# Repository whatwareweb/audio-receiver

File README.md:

# audio-receiver
OSHW audio reciever and amplifier

### What is it
This is an audio receiver and amplifier with a classic design. I built it because I wanted to learn more about Class AB amplifier design and analog circuitry in general.

### Why use it
Class-D amplifiers, as used in receivers these days, offer lots of power, but the sound quality can be lacking.

Class-AB amplifiers, while less efficient and therefore harder to get high power output, have overall less distortion and can offer a better signal-to-noise ratio if designed properly.

The design of the amplifier portion is similar to amplifiers built in the so-called "Golden age" of Hi-fi audio, in the 70s and 80s. I wanted a Class-AB amplifier that had the great sound quality of products from times gone by, but with modern features such as digital screens, and without the clunky mechanical interfaces of older receivers.

### Goals
My goals for this project were to have good sound quality with modern features, and also to use industry standard practices for receiver assembly to make it easy to assemble.

### Features
 - Stereo audio amplifier
 - 4 input channels
 - Volume control
 - Digitally selectable inputs
 - OLED display with renamable inputs
 - 15w per channel output
 - All-analog signal path
 - 3 separate PCBs for low noise

### Usage
It is super simple, just hook up a line level signal to the RCA jacks on the back, and select your input and you're good to go!

### Wiring
To wire up the internal parts, simply connect the +/-5v line from the first power supply to the input board, the +5v line to the control board, and the +36v line from the 2nd power supply to the amplifier board, as shown in the PCB silkscreen. Then, using the Phoenix cables in the BOM, connect the Phoenix connectors together. 

### PCB screenshots

## BOM
|Qty|Value                          |Mouser URL                                                                                                                             |Mouser PN            |price|lumped price|
|---|-------------------------------|---------------------------------------------------------------------------------------------------------------------------------------|---------------------|-----|------------|
|2  |10uF                           |https://www.mouser.com/ProductDetail/Wurth-Elektronik/860020672010?qs=sGAEpiMZZMsh%252B1woXyUXj4jKQI6sNRw6%252B%2FnWw7D23Ww%3D         |710-860020672010     |0.11 |0.22        |
|6  |100uF                          |https://www.mouser.com/ProductDetail/Nichicon/UVR1H101MPD1TD?qs=sGAEpiMZZMsh%252B1woXyUXj9Qfu%2FLgQWnHf9Zyy1TLY94%3D                   |647-UVR1H101MPD1TD   |0.25 |1.5         |
|2  |100pF                          |https://www.mouser.com/ProductDetail/Walsin/YP501101K040BAND5P?qs=sGAEpiMZZMsh%252B1woXyUXj9Vc%2FsqQGnyVc97Ek7nEcX0%3D                 |791-YP501101K40AND5  |0.11 |0.22        |
|2  |2200uF                         |https://www.mouser.com/ProductDetail/Rubycon/35YXJ2200M16X25?qs=sGAEpiMZZMsh%252B1woXyUXj57M5zdvZVAFuY6LrCottNI%3D                     |232-35YXJ2200M16X25  |1.15 |2.3         |
|2  |33uF                           |https://www.mouser.com/ProductDetail/Wurth-Elektronik/860010672011?qs=sGAEpiMZZMsh%252B1woXyUXj4jKQI6sNRw6%2FzsPRxKesag%3D             |710-860010672011     |0.12 |0.24        |
|2  |100nF                          |https://www.mouser.com/ProductDetail/Walsin/YV101103Z060HAND5P?qs=sGAEpiMZZMsh%252B1woXyUXj9Vc%2FsqQGnyVkbUw7FMjgKQ%3D                 |791-YV101103Z60HAND5 |0.1  |0.2         |
|8  |1N4148                         |https://www.mouser.com/ProductDetail/onsemi-Fairchild/1N4148-T50R?qs=sGAEpiMZZMtbRapU8LlZD%252B6h%2FWulpAkrNJDKqwRgmZcB5SlWjKcc2w%3D%3D|512-1N4148T50R       |0.1  |0.8         |
|8  |UF4004                         |https://www.mouser.com/ProductDetail/Diotec-Semiconductor/UF4004?qs=OlC7AqGiEDlRgKmeDlLF1Q%3D%3D                                       |637-UF4004           |0.12 |0.96        |
|1  |Fuse Holder                    |https://www.mouser.com/ProductDetail/Eaton-Electronics/BK-1A5601?qs=sfCJykTDjbAGESUvg%2FlMZw%3D%3D                                     |504-1A5601           |0.5  |0.5         |
|1  |Screw_Terminal_01x03           |https://www.mouser.com/ProductDetail/Phoenix-Contact/1757255?qs=uD%2FdkN7XIa0ez8xszzicKg%3D%3D                                         |651-1757255          |0.93 |0.93        |
|1  |Screw_Terminal_01x04           |https://www.mouser.com/ProductDetail/Same-Sky/TB007-508-04BE?qs=vLWxofP3U2wnrmN2C1kFLw%3D%3D                                           |490-TB007-508-04BE   |0.94 |0.94        |
|1  |Screw_Terminal_01x02           |https://www.mouser.com/ProductDetail/Same-Sky/TB007-508-02BE?qs=vLWxofP3U2y6PFKAfCqKUQ%3D%3D                                           |490-TB007-508-02BE   |0.49 |0.49        |
|2  |BC559                          |https://www.mouser.com/ProductDetail/Diotec-Semiconductor/BC559A?qs=OlC7AqGiEDlWVUSYP2ErFQ%3D%3D                                       |637-BC559A           |0.1  |0.2         |
|4  |BD139                          |https://www.mouser.com/ProductDetail/STMicroelectronics/BD139-16?qs=RfHREzyZwW%252BVwEMhVd3zpQ%3D%3D                                   |511-BD139-16         |0.62 |2.48        |
|2  |BD140                          |https://www.mouser.com/ProductDetail/STMicroelectronics/BD140-16?qs=RfHREzyZwW%252BkgnSLCtGbjg%3D%3D                                   |511-BD140-16         |0.45 |0.9         |
|2  |MJE3055                        |https://www.mouser.com/ProductDetail/onsemi/MJE3055TG?qs=HVbQlW5zcXUpZ6jjVRRo8A%3D%3D                                                  |863-MJE3055TG        |0.85 |1.7         |
|2  |MJE2955                        |https://www.mouser.com/ProductDetail/onsemi/MJE2955TG?qs=HVbQlW5zcXV0Q1cBURTsUg%3D%3D                                                  |863-MJE2955TG        |1.23 |2.46        |
|4  |33k                            |https://www.mouser.com/ProductDetail/YAGEO/MFR-25FTF52-33K?qs=gt1LBUVyoHmEHRwLqpWLLA%3D%3D                                             |603-MFR-25FTF52-33K  |0.1  |0.4         |
|8  |2k2                            |https://www.mouser.com/ProductDetail/YAGEO/MF0207FTE52-2K2?qs=KUIzHt%2Fe91lZCf2OHy2lbw%3D%3D                                           |603-MF0207FTE52-2K2  |0.1  |0.8         |
|2  |100R                           |https://www.mouser.com/ProductDetail/YAGEO/MFR-12FTF52-100R?qs=oAGoVhmvjhzHogggiomzAA%3D%3D                                            |603-MFR-12FTF52-100R |0.1  |0.2         |
|2  |1k                             |https://www.mouser.com/ProductDetail/YAGEO/MFR-25FTF52-1K?qs=Uzd%2Fwh%252BZzhBCS7HxlKfPkQ%3D%3D                                        |603-MFR-25FTF52-1K   |0.1  |0.2         |
|2  |560                            |https://www.mouser.com/ProductDetail/YAGEO/FMP200JR-52-560R?qs=wcZjbqjoJehIyDJh2zs3Bw%3D%3D                                            |603-FMP200JR-52-560R |0.15 |0.3         |
|4  |2R7                            |https://www.mouser.com/ProductDetail/YAGEO/SQP500JB-2R7?qs=sGAEpiMZZMsPqMdJzcrNwl88Wd0KdECunjP3GAgCqls%3D                              |603-SQP500JB-2R7     |0.54 |2.16        |
|2  |12k                            |https://www.mouser.com/ProductDetail/YAGEO/MFR25SFTF26-12K?qs=sGAEpiMZZMsPqMdJzcrNwqpmsrDQJrmxnqH2%2F1fJqXZRHayDc4k%252B4A%3D%3D       |603-MFR25SFTF26-12K  |0.1  |0.2         |
|2  |2R7                            |https://www.mouser.com/ProductDetail/YAGEO/CFR-25JR-52-2R7?qs=sGAEpiMZZMsPqMdJzcrNwiPCnpFTGbbhiVnCR3xqnQk%3D                           |603-CFR-25JR-52-2R7  |0.1  |0.2         |
|2  |100nF                          |https://www.mouser.com/ProductDetail/Walsin/RD21B104K500A5HAND?qs=ZrPdAQfJ6DNDZtFW9mG29g%3D%3D                                         |791-RD21B104K500A5HA |0.19 |0.38        |
|2  |10uF                           |https://www.mouser.com/ProductDetail/TDK/FG28X5R1E106MRT06?qs=LtAzLad%252BoeUoMYHhhxs3zA%3D%3D                                         |810-FG28X5R1E106MR06 |0.45 |0.9         |
|1  |PJRAS4X2U01AUX                 |https://www.mouser.com/ProductDetail/Switchcraft/PJRAS4X2U01X?qs=mcPJWgAPNreWN%252BuSt4UsAA%3D%3D                                      |502-PJRAS4X2U01X     |5.22 |5.22        |
|1  |Screw_Terminal_01x04           |https://www.mouser.com/ProductDetail/Phoenix-Contact/1757268?qs=uD%2FdkN7XIa2BicmSj3mD7g%3D%3D                                         |651-1757268          |1.26 |1.26        |
|1  |Screw_Terminal_01x03           |https://www.mouser.com/ProductDetail/Phoenix-Contact/1757255?qs=uD%2FdkN7XIa0ez8xszzicKg%3D%3D                                         |651-1757255          |0.93 |0.93        |
|1  |Screw_Terminal_01x03           |https://www.mouser.com/ProductDetail/Same-Sky/TB007-508-03BE?qs=vLWxofP3U2zHYiGqNs1vAA%3D%3D                                           |490-TB007-508-03BE   |0.72 |0.72        |
|1  |CD4052B                        |https://www.mouser.com/c/?q=595-CD4052BE                                                                                               |595-CD4052BE         |0.6  |0.6         |
|1  |100nF                          |https://www.mouser.com/ProductDetail/Walsin/RD21B104K500A5HAND?qs=ZrPdAQfJ6DNDZtFW9mG29g%3D%3D                                         |791-RD21B104K500A5HA |0.19 |0.19        |
|1  |Screw_Terminal_01x04           |https://www.mouser.com/ProductDetail/Phoenix-Contact/1757268?qs=uD%2FdkN7XIa2BicmSj3mD7g%3D%3D                                         |651-1757268          |1.26 |1.26        |
|1  |Screw_Terminal_01x02           |https://www.mouser.com/ProductDetail/Same-Sky/TB007-508-02BE?qs=vLWxofP3U2y6PFKAfCqKUQ%3D%3D                                           |490-TB007-508-02BE   |0.49 |0.49        |
|5  |SW_Push                        |https://www.mouser.com/ProductDetail/Same-Sky/TS02-66-55-BK-260-LCR-D?qs=A6eO%252BMLsxmT6x4NEvNu8bQ%3D%3D                              |179-TS026655BK260LCR |0.1  |0.5         |
|1  |ATtiny84A-SS                   |https://www.mouser.com/ProductDetail/Microchip-Technology/ATTINY84A-SSFR?qs=TI%2F9gtmDCEEVjKMalwq6aQ%3D%3D                             |556-ATTINY84A-SSFR   |1.08 |1.08        |
|4  |heatsinks                      |https://www.mouser.com/ProductDetail/Same-Sky/HSS-B20-NP-12?qs=u4fy%2FsgLU9Mva%2Fp9%252ByZBdw%3D%3D                                    |n/a                  |0.59 |2.36        |
|1  |m3 bolts                       |https://www.homedepot.com/p/Hillman-M3-0-5-x-10-mm-Internal-Hex-Button-Head-Cap-Screws-20-Pack-44456/204801187                         |n/a                  |5.74 |5.74        |
|1  |m3 nuts                        |https://www.homedepot.com/p/Hillman-Metric-Hex-Nuts-M3-x-0-50-Coarse-Thread-4053/204801247                                             |n/a                  |6.62 |6.62        |
|1  |fuse holder                    |https://www.mouser.com/ProductDetail/Eaton-Electronics/BK-1A5601?qs=sfCJykTDjbAGESUvg%2FlMZw%3D%3D                                     |n/a                  |0.5  |0.5         |
|2  |fuses                          |https://www.mouser.com/ProductDetail/Schurter/0034.1519?qs=ar9f0rk5DXBZIZv2oGoEHA%3D%3D                                                |n/a                  |0.47 |0.94        |
|2  |red terminal post              |https://www.mouser.com/ProductDetail/SparkFun/PRT-09739?qs=WyAARYrbSnb2d3ZiFmZgWQ%3D%3D                                                |n/a                  |0.75 |1.5         |
|2  |black terminal post            |https://www.mouser.com/ProductDetail/SparkFun/PRT-09740?qs=WyAARYrbSnbVb9GdE8xnVA%3D%3D                                                |n/a                  |0.75 |1.5         |
|2  |internal phoenix connector 3pin|https://www.mouser.com/ProductDetail/Phoenix-Contact/1757022?qs=sGAEpiMZZMvlX3nhDDO4ANTLkcKs1Zj3jcphtS8o9Tk%3D                         |n/a                  |2.89 |5.78        |
|2  |internal phoenix connector 4pin|https://www.mouser.com/ProductDetail/Phoenix-Contact/1757035?qs=sGAEpiMZZMvlX3nhDDO4AH7PhxHWF%252BlKb5jy%252B%2F%252BeCXE%3D           |n/a                  |3.85 |7.7         |
|1  |fan                            |https://a.co/d/h5aS2CF                                                                                                                 |n/a                  |15.95|15.95       |
|1  |dip16 socket                   |https://www.mouser.com/ProductDetail/TE-Connectivity/1-2199298-4?qs=fK8dlpkaUMvpL10rY9Abiw%3D%3D                                       |n/a                  |0.25 |0.25        |
|1  |36v psu                        |https://www.mouser.com/ProductDetail/MEAN-WELL/LRS-150-36?qs=vDxCgdWo2h82V5jS5IXvUQ%3D%3D                                              |n/a                  |19.8 |19.8        |
|1  |+ / - 5v psu                   |https://www.mouser.com/ProductDetail/MEAN-WELL/PD-2505?qs=V9a8iPeg90ze2O5SXmOiQQ%3D%3D                                                 |n/a                  |16   |16          |
|1  |oled display                   |https://a.co/d/fhCKttE                                                                                                                 |n/a                  |6.29 |6.29        |
|1  |Input switcher PCB             |n/a – pcbway                                                                                                                           |n/a                  |5    |5           |
|1  |control board pcb              |n/a – pcbway                                                                                                                           |n/a                  |5    |5           |
|1  |amp board pcb                  |n/a – pcbway                                                                                                                           |n/a                  |27.78|27.78       |
|   |                               |                                                                                                                                       |                     |     |            |
|   |                               |                                                                                                                                       |                     |     |            |
|   |                               |                                                                                                                                       |                     |     |            |
|   |                               |                                                                                                                                       |                     |     |            |
|   |                               |                                                                                                                                       |                     |     |            |
|   |                               |                                                                                                                                       |                     |     |            |
|   |                               |                                                                                                                                       |                     |     |            |
|   |Total                          |                                                                                                                                       |                     |     |            |
|   |163.74                         |                                                                                                                                       |                     |     |            |

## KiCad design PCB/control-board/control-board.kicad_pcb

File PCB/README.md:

# audio-receiver
OSHW audio reciever and amplifier

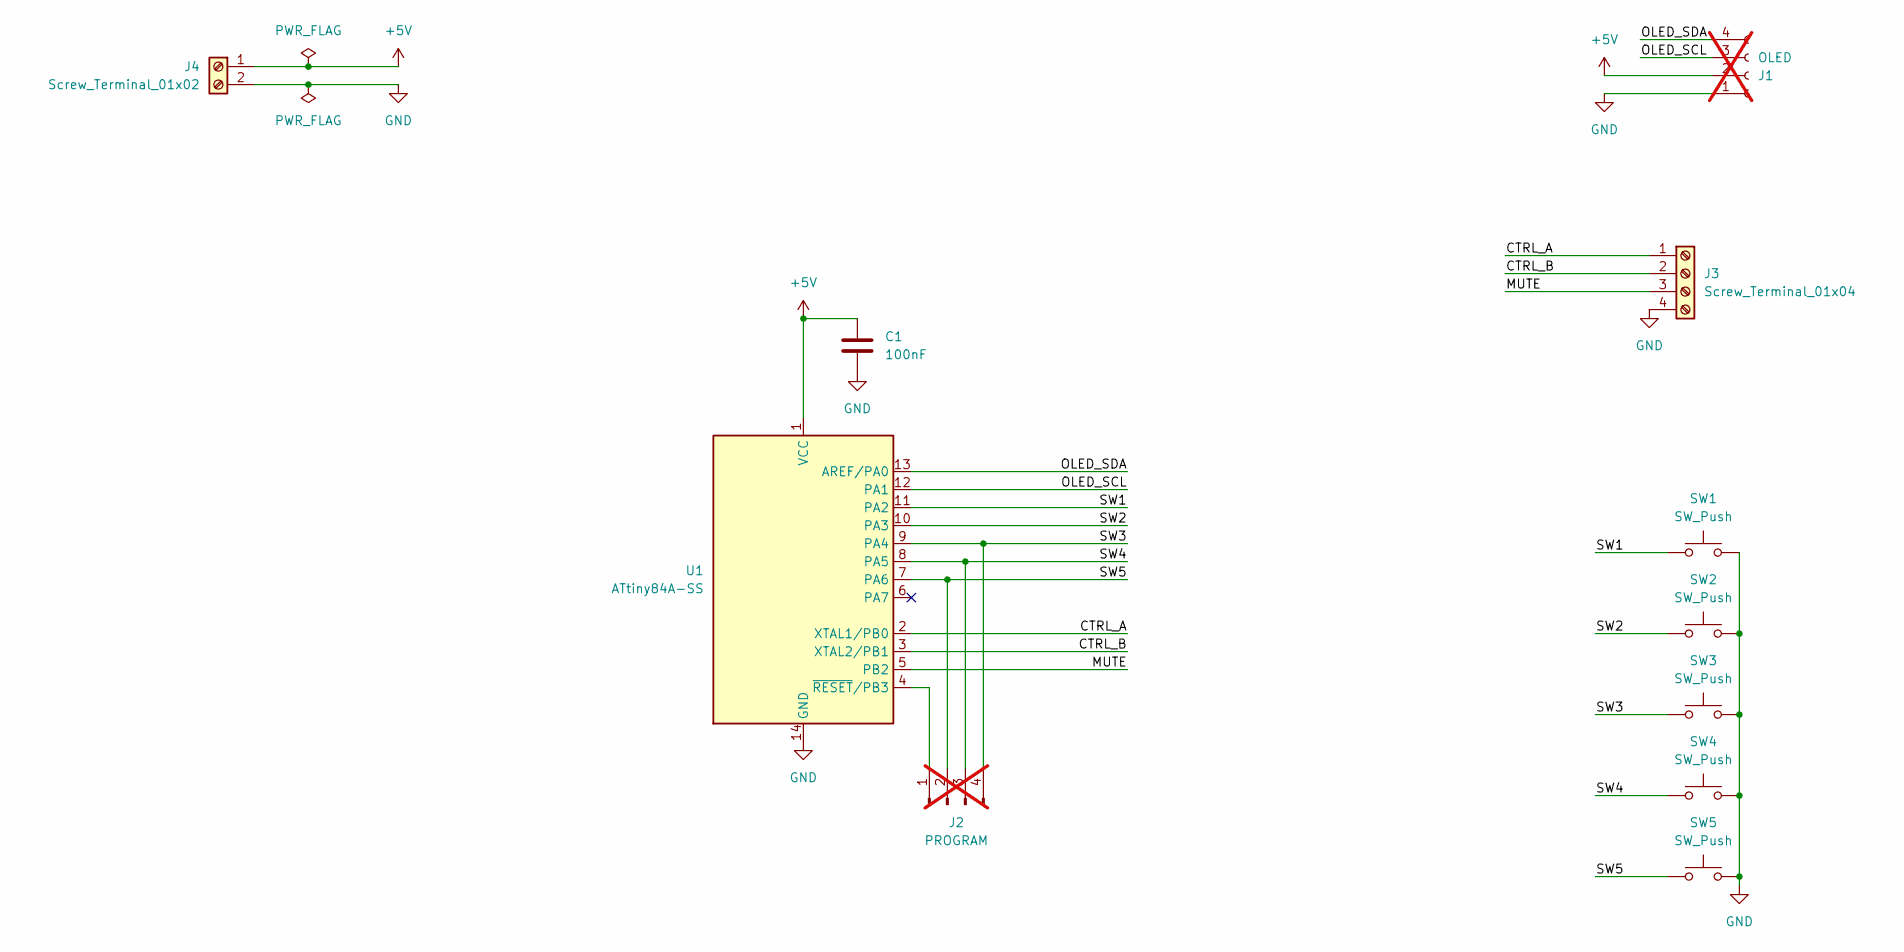
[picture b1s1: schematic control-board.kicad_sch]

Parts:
C1: 100nF; C_Disc_D6.0mm_W2.5mm_P5.00mm; Mouser PN 791-RD21B104K500A5HA
J1: OLED; SSD1306-0.91-OLED-4pin-128x32; not fitted
J2: PROGRAM; PinHeader_1x04_P2.54mm_Vertical; not fitted
J3: Screw_Terminal_01x04; PhoenixContact_MSTBA_2,5_4-G-5,08_1x04_P5.08mm_Horizontal; Mouser PN 651-1757268
J4: Screw_Terminal_01x02; TerminalBlock_CUI_TB007-508-02_1x02_P5.08mm_Horizontal; Mouser PN 490-TB007-508-02BE
SW1, SW2, SW3, SW4, SW5: SW_Push; SW_PUSH_6mm; Mouser PN 179-TS026655BK260LCR
U1: ATtiny84A-SS; SOIC-14_3.9x8.7mm_P1.27mm; Mouser PN 556-ATTINY84A-SSFR

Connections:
+5V: C1.1, J1.2, J4.1, U1.1 (VCC)
/CTRL_A: J3.1, U1.2 (XTAL1/PB0)
/CTRL_B: J3.2, U1.3 (XTAL2/PB1)
/MUTE: J3.3, U1.5 (PB2)
/OLED_SCL: J1.3, U1.12 (PA1)
/OLED_SDA: J1.4, U1.13 (AREF/PA0)
/SW1: SW1.1, U1.11 (PA2)
/SW2: SW2.1, U1.10 (PA3)
/SW3: J2.4, SW3.1, U1.9 (PA4)
/SW4: J2.3, SW4.1, U1.8 (PA5)
/SW5: J2.2, SW5.1, U1.7 (PA6)
GND: C1.2, J1.1, J3.4, J4.2, SW1.2, SW2.2, SW3.2, SW4.2, SW5.2, U1.14 (GND)
unnamed: J2.1, U1.4 (~RESET/PB3)

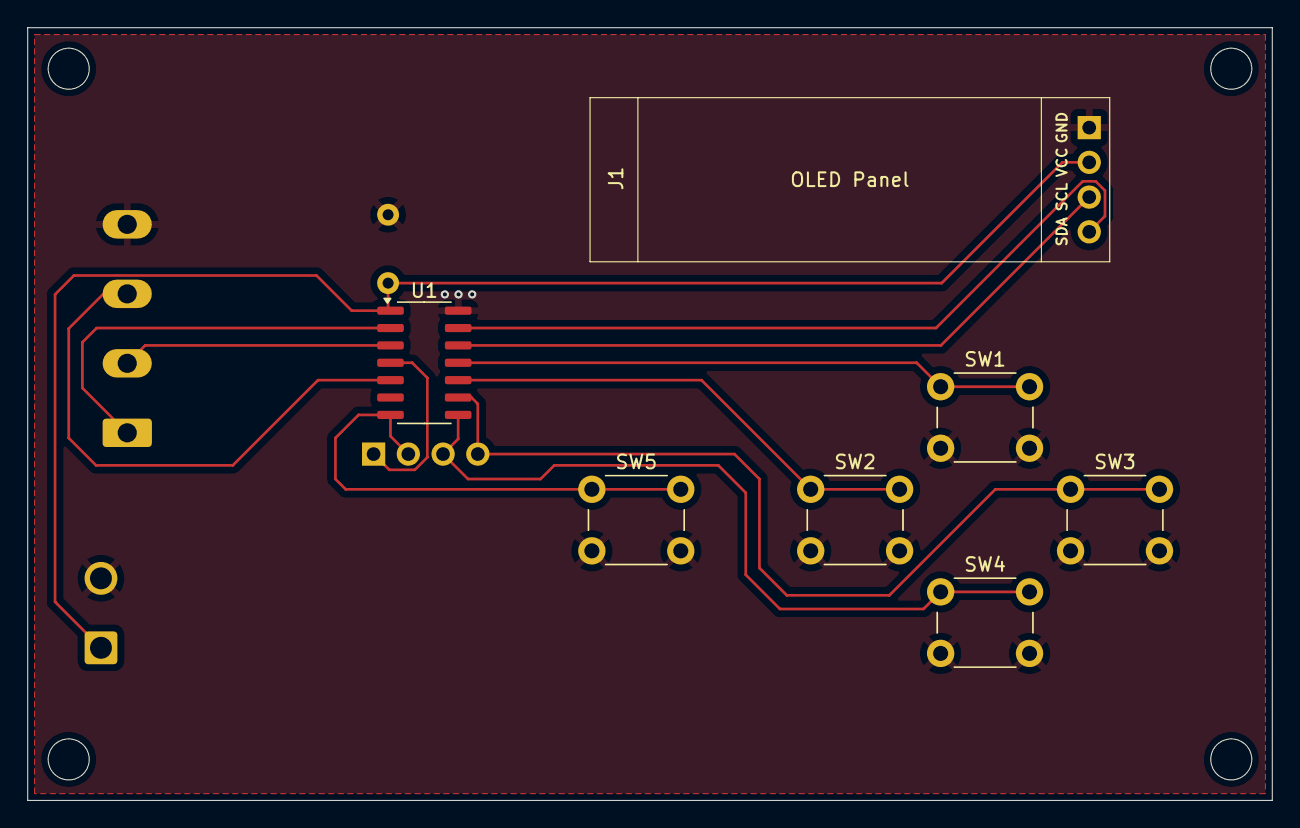
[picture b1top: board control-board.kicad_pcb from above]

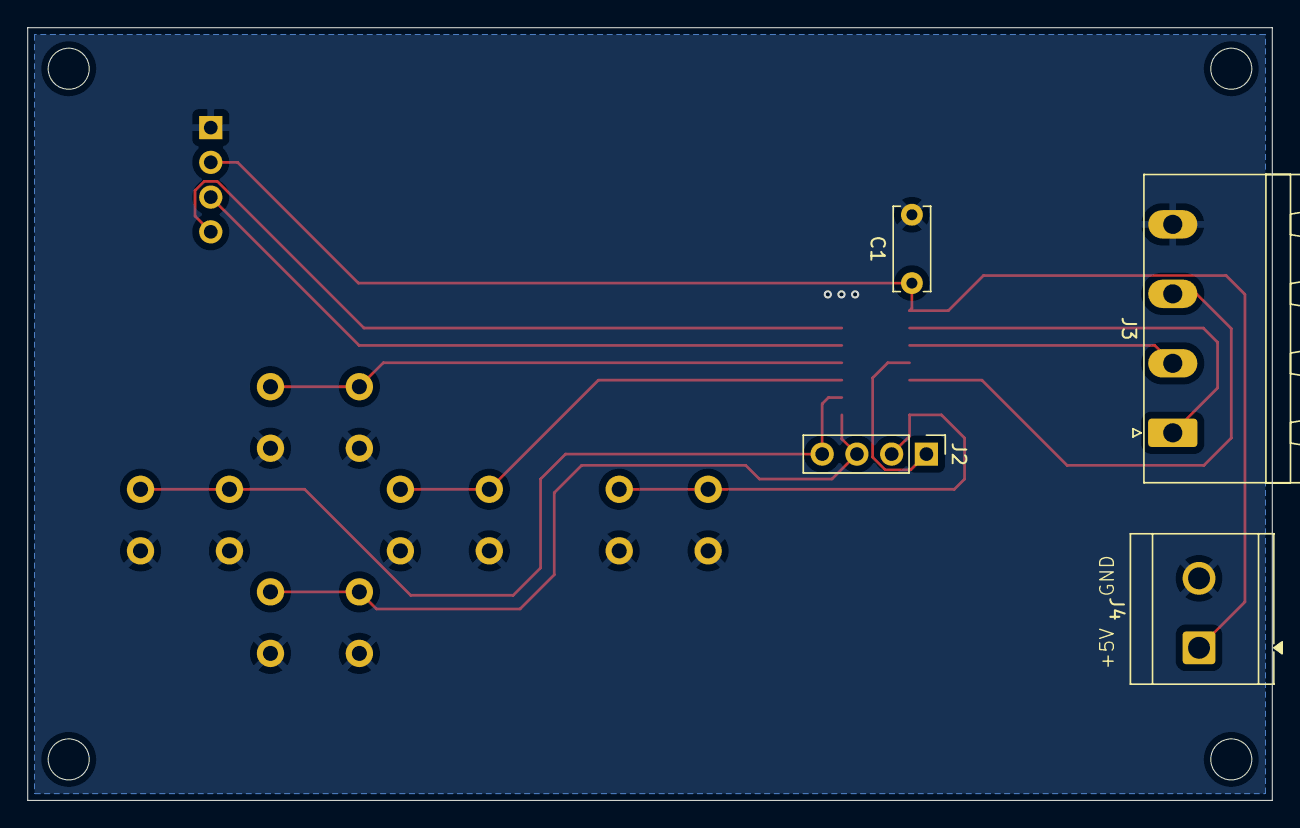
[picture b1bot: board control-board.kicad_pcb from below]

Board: 2 copper layers, 91.0 x 56.5 mm, 11 parts (4 on the bottom side), 13 nets.

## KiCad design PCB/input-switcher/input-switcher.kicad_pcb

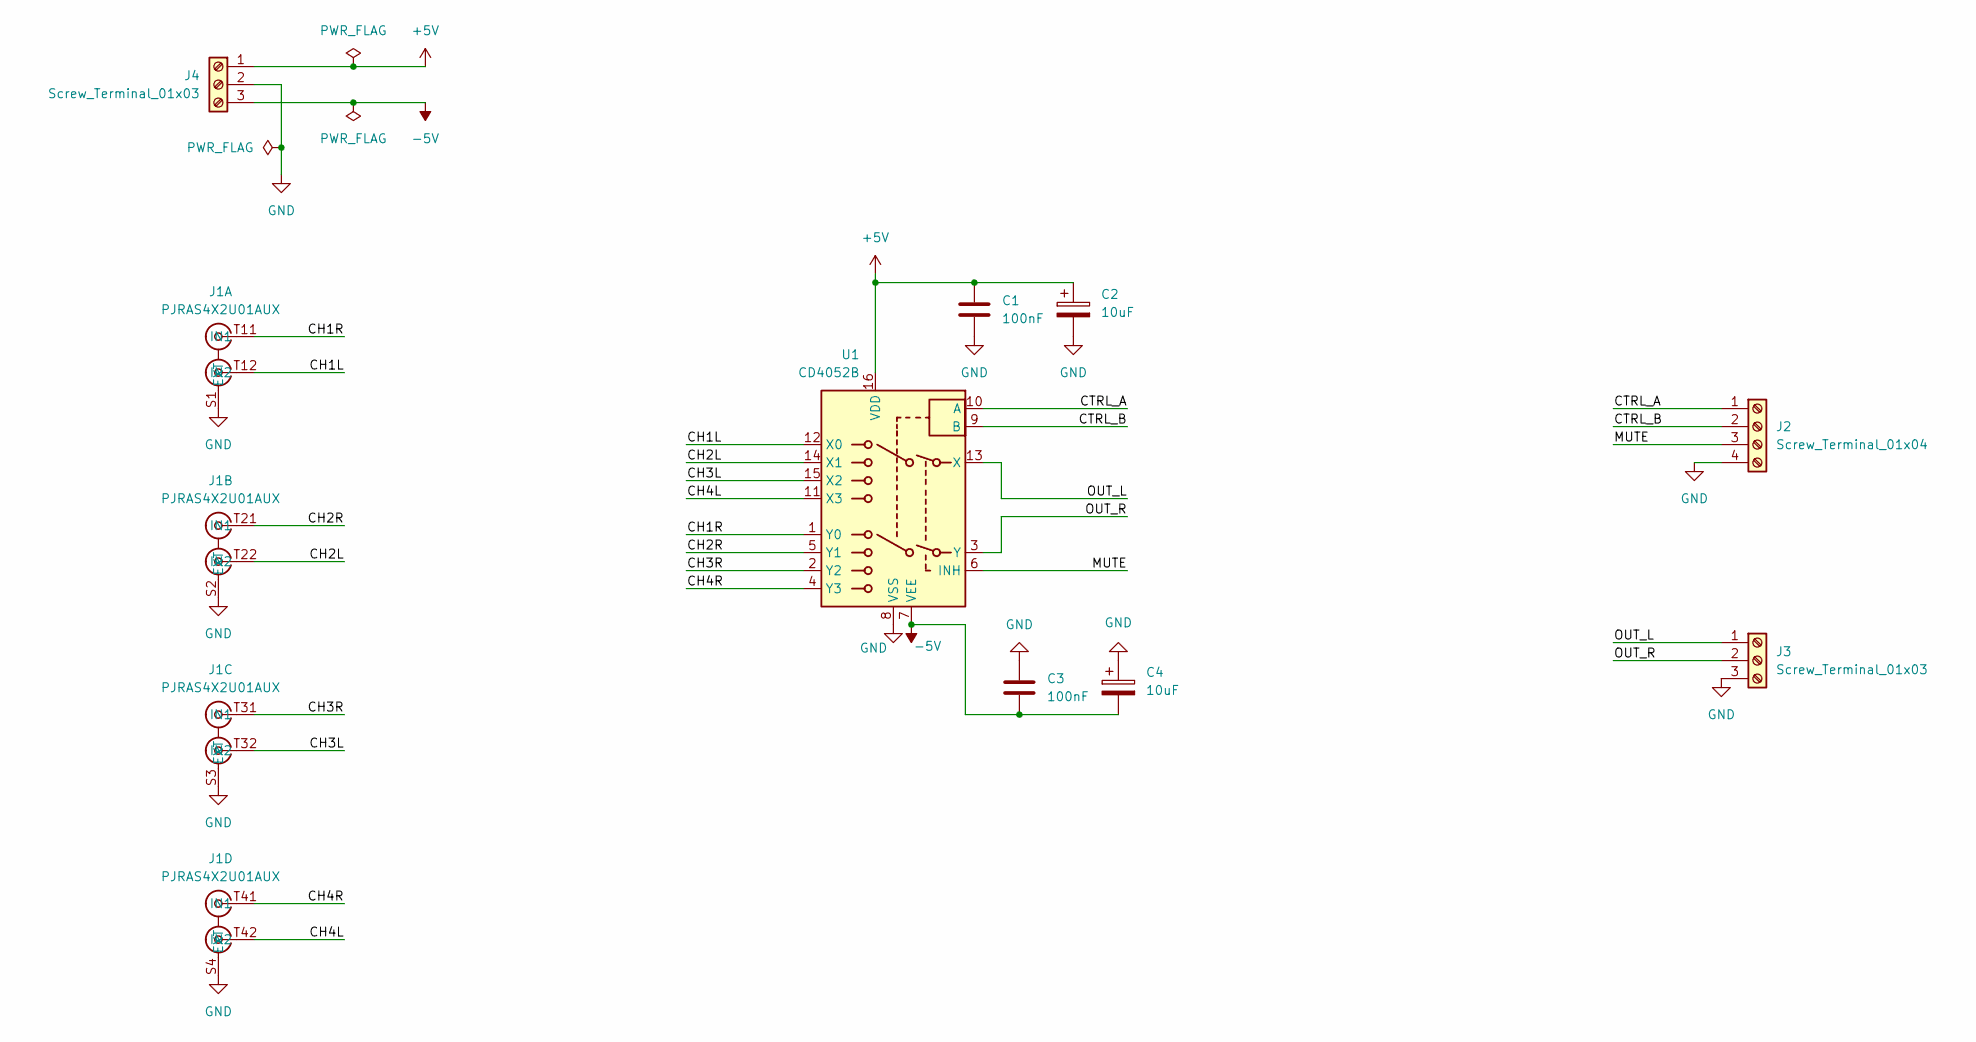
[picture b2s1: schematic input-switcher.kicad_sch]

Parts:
C1, C3: 100nF; C_Disc_D6.0mm_W2.5mm_P5.00mm; Mouser PN 791-RD21B104K500A5HA
C2, C4: 10uF; C_Rect_L7.0mm_W2.5mm_P5.00mm; Mouser PN 810-FG28X5R1E106MR06
J1: PJRAS4X2U01AUX; Mouser Part Number 502-PJRAS4X2U01AUX
J2: Screw_Terminal_01x04; PhoenixContact_MSTBA_2,5_4-G-5,08_1x04_P5.08mm_Horizontal; Mouser PN 651-1757268
J3: Screw_Terminal_01x03; PhoenixContact_MSTBA_2,5_3-G-5,08_1x03_P5.08mm_Horizontal; Mouser PN 651-1757255
J4: Screw_Terminal_01x03; TerminalBlock_CUI_TB007-508-03_1x03_P5.08mm_Horizontal; Mouser PN 490-TB007-508-03BE
U1: CD4052B; DIP-16_W7.62mm_Socket; Mouser PN 595-CD4052BE

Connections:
+5V: C1.1, C2.1, J4.1, U1.16 (VDD)
-5V: C3.2, C4.2, J4.3, U1.7 (VEE)
/CH1L: J1.T12 (IN2), U1.12 (X0)
/CH1R: J1.T11 (IN1), U1.1 (Y0)
/CH2L: J1.T22 (IN2), U1.14 (X1)
/CH2R: J1.T21 (IN1), U1.5 (Y1)
/CH3L: J1.T32 (IN2), U1.15 (X2)
/CH3R: J1.T31 (IN1), U1.2 (Y2)
/CH4L: J1.T42 (IN2), U1.11 (X3)
/CH4R: J1.T41 (IN1), U1.4 (Y3)
/CTRL_A: J2.1, U1.10 (A)
/CTRL_B: J2.2, U1.9 (B)
/MUTE: J2.3, U1.6 (INH)
/OUT_L: J3.1, U1.13 (X)
/OUT_R: J3.2, U1.3 (Y)
GND: C1.2, C2.2, C3.1, C4.1, J1.S1 (EXT), J1.S2 (EXT), J1.S3 (EXT), J1.S4 (EXT), J2.4, J3.3, J4.2, U1.8 (VSS)

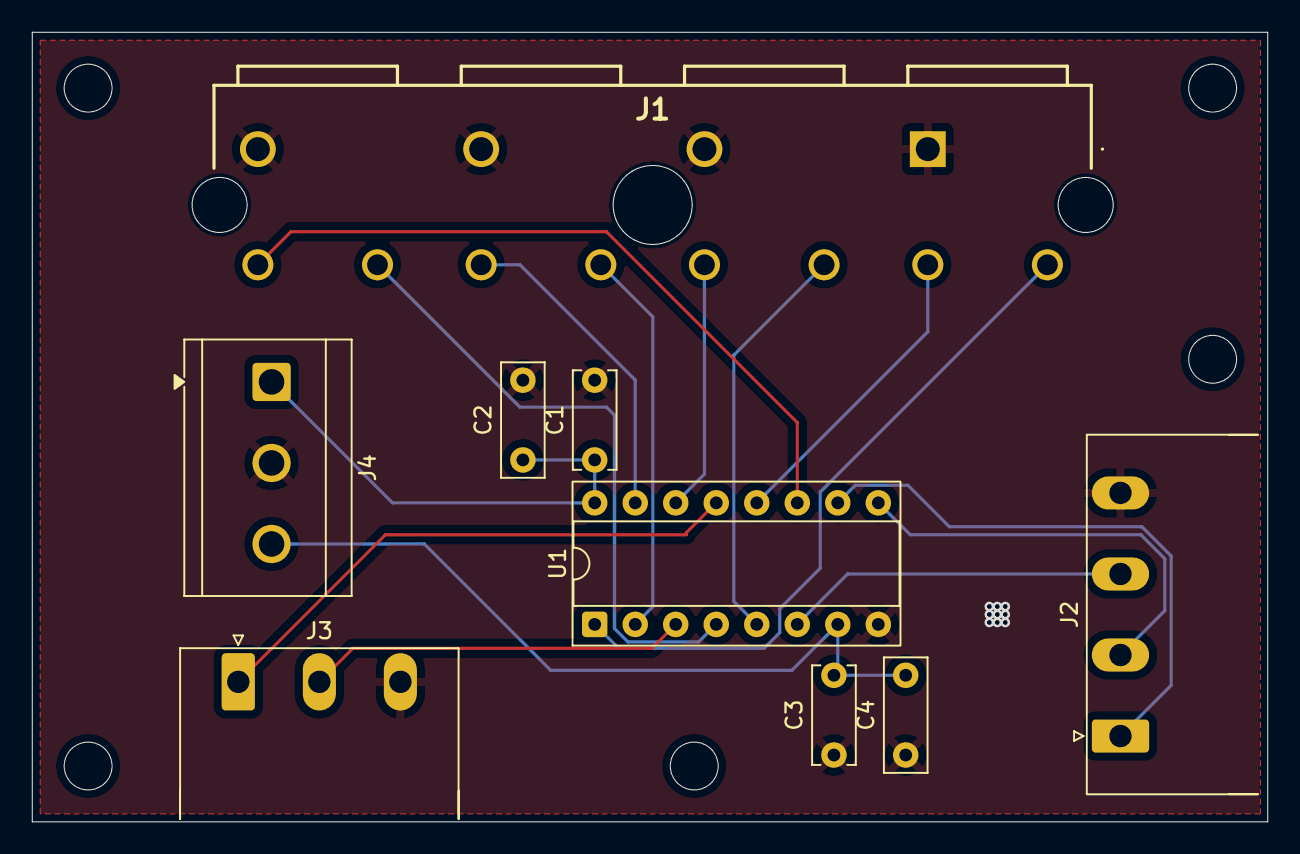
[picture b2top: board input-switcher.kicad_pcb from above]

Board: 2 copper layers, 77.5 x 49.5 mm, 9 parts (0 on the bottom side), 16 nets.

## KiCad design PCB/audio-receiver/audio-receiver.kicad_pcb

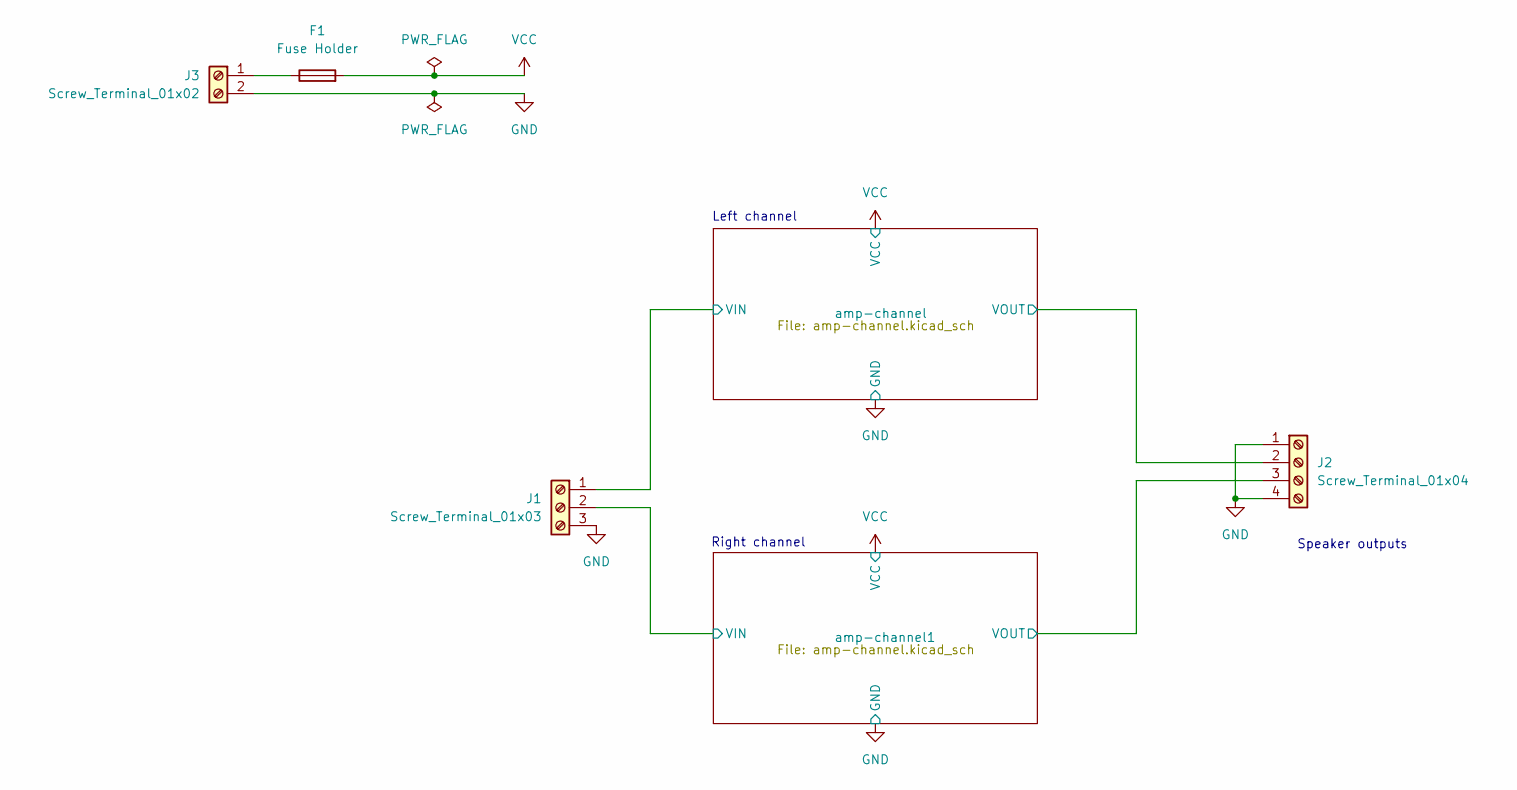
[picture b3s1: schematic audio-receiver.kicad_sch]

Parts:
F1: Fuse Holder; Fuseholder_Clip-5x20mm_Eaton_1A5601-01_Inline_P20.80x6.76mm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; Mouser PN 504-1A5601
J1: Screw_Terminal_01x03; PhoenixContact_MSTBA_2,5_3-G-5,08_1x03_P5.08mm_Horizontal; Mouser PN 651-1757255
J2: Screw_Terminal_01x04; TerminalBlock_CUI_TB007-508-04_1x04_P5.08mm_Horizontal; Mouser PN 490-TB007-508-04BE
J3: Screw_Terminal_01x02; TerminalBlock_CUI_TB007-508-02_1x02_P5.08mm_Horizontal; Mouser PN 490-TB007-508-02BE

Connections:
/amp-channel1/VIN: J1.2; also elsewhere on the board
/amp-channel1/VOUT: J2.3; also elsewhere on the board
/amp-channel/VIN: J1.1; also elsewhere on the board
/amp-channel/VOUT: J2.2; also elsewhere on the board
GND: J1.3, J2.1, J2.4, J3.2; also elsewhere on the board
unnamed: F1.1, J3.1
VCC: F1.2; also elsewhere on the board

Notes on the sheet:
Left channel
Speaker outputs
Right channel

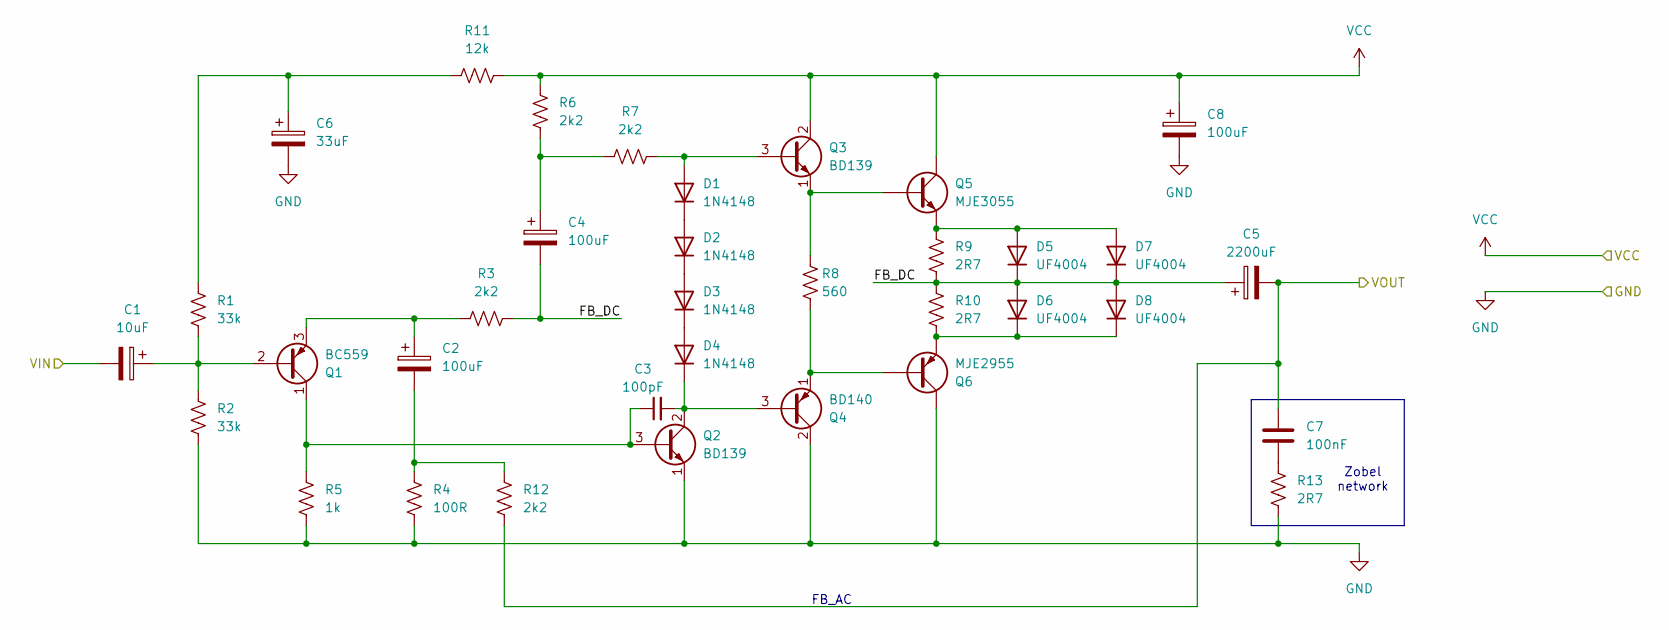
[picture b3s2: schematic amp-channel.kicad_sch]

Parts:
C1: 10uF; CP_Radial_D5.0mm_P2.00mm; Mouser PN 710-860020672010
C2, C4, C8: 100uF; CP_Radial_D8.0mm_P3.50mm; Mouser PN 647-UVR1H101MPD1TD
C3: 100pF; C_Disc_D4.3mm_W1.9mm_P5.00mm; Mouser PN 791-YP501101K40AND5
C5: 2200uF; CP_Radial_D16.0mm_P7.50mm; Mouser PN 232-35YXJ2200M16X25
C6: 33uF; CP_Radial_D5.0mm_P2.00mm; Mouser PN 710-860010672011
C7: 100nF; C_Disc_D4.3mm_W1.9mm_P5.00mm; Mouser PN 791-YV101103Z60HAND5
D1, D2, D3, D4: 1N4148; D_DO-35_SOD27_P7.62mm_Horizontal; Mouser PN 512-1N4148T50R
D5, D6, D7, D8: UF4004; D_DO-41_SOD81_P7.62mm_Horizontal; Mouser PN 637-UF4004
Q1: BC559; TO-92_Inline_Wide; Mouser PN 637-BC559A
Q2, Q3: BD139; TO-126-3_Vertical; Mouser PN 511-BD139-16
Q4: BD140; TO-126-3_Vertical; Mouser PN 511-BD140-16
Q5: MJE3055; TO-220-3_Vertical; Mouser PN 863-MJE3055TG
Q6: MJE2955; TO-220-3_Vertical; Mouser PN 863-MJE2955TG
R1, R2: 33k; R_Axial_DIN0207_L6.3mm_D2.5mm_P7.62mm_Horizontal; Mouser PN 603-MFR-25FTF52-33K
R3, R6, R7, R12: 2k2; R_Axial_DIN0207_L6.3mm_D2.5mm_P7.62mm_Horizontal; Mouser PN 603-MF0207FTE52-2K2
R4: 100R; R_Axial_DIN0204_L3.6mm_D1.6mm_P5.08mm_Horizontal; Mouser PN 603-MFR-12FTF52-100R
R5: 1k; R_Axial_DIN0207_L6.3mm_D2.5mm_P7.62mm_Horizontal; Mouser PN 603-MFR-25FTF52-1K
R8: 560; R_Axial_DIN0309_L9.0mm_D3.2mm_P12.70mm_Horizontal; Mouser PN 603-FMP200JR-52-560R
R9, R10: 2R7; R_Axial_Power_L25.0mm_W9.0mm_P27.94mm; Mouser PN 603-SQP500JB-2R7
R11: 12k; R_Axial_DIN0207_L6.3mm_D2.5mm_P7.62mm_Horizontal; Mouser PN 603-MFR25SFTF26-12K
R13: 2R7; R_Axial_DIN0207_L6.3mm_D2.5mm_P7.62mm_Horizontal; Mouser PN 603-CFR-25JR-52-2R7

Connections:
/amp-channel/FB_DC: C4.2, C5.1, D5.1 (K), D6.2 (A), D7.1 (K), D8.2 (A), R3.2, R9.2, R10.1
/amp-channel/VIN: C1.2; also elsewhere on the board
/amp-channel/VOUT: C5.2, C7.1, R12.2; also elsewhere on the board
GND: C6.2, C8.2, Q2.1 (E), Q4.2 (C), Q6.2 (C), R2.2, R4.2, R5.2, R13.2; also elsewhere on the board
unnamed: C2.2, R4.1, R12.1
unnamed: C4.1, R6.2, R7.1
unnamed: C6.1, R1.1, R11.1
unnamed: C7.2, R13.1
unnamed: D1.2 (A), Q3.3 (B), R7.2
unnamed: D1.1 (K), D2.2 (A)
unnamed: D2.1 (K), D3.2 (A)
unnamed: D3.1 (K), D4.2 (A)
unnamed: C3.2, D4.1 (K), Q2.2 (C), Q4.3 (B)
unnamed: D5.2 (A), D7.2 (A), Q5.3 (E), R9.1
unnamed: D6.1 (K), D8.1 (K), Q6.3 (E), R10.2
unnamed: C1.1, Q1.2 (B), R1.2, R2.1
unnamed: C3.1, Q1.1 (C), Q2.3 (B), R5.1
unnamed: C2.1, Q1.3 (E), R3.1
unnamed: Q3.1 (E), Q5.1 (B), R8.1
unnamed: Q4.1 (E), Q6.1 (B), R8.2
VCC: C8.1, Q3.2 (C), Q5.2 (C), R6.1, R11.2; also elsewhere on the board

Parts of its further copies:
C9: 10uF; CP_Radial_D5.0mm_P2.00mm; Mouser PN 710-860020672010
C10: 33uF; CP_Radial_D5.0mm_P2.00mm; Mouser PN 710-860010672011
C11, C12, C14: 100uF; CP_Radial_D8.0mm_P3.50mm; Mouser PN 647-UVR1H101MPD1TD
C13: 100pF; C_Disc_D4.3mm_W1.9mm_P5.00mm; Mouser PN 791-YP501101K40AND5
C15: 2200uF; CP_Radial_D16.0mm_P7.50mm; Mouser PN 232-35YXJ2200M16X25
C16: 100nF; C_Disc_D4.3mm_W1.9mm_P5.00mm; Mouser PN 791-YV101103Z60HAND5
D9, D10, D11, D12: 1N4148; D_DO-35_SOD27_P7.62mm_Horizontal; Mouser PN 512-1N4148T50R
D13, D14, D15, D16: UF4004; D_DO-41_SOD81_P7.62mm_Horizontal; Mouser PN 637-UF4004
Q7: BC559; TO-92_Inline_Wide; Mouser PN 637-BC559A
Q8, Q9: BD139; TO-126-3_Vertical; Mouser PN 511-BD139-16
Q10: BD140; TO-126-3_Vertical; Mouser PN 511-BD140-16
Q11: MJE3055; TO-220-3_Vertical; Mouser PN 863-MJE3055TG
Q12: MJE2955; TO-220-3_Vertical; Mouser PN 863-MJE2955TG
R14, R15: 33k; R_Axial_DIN0207_L6.3mm_D2.5mm_P7.62mm_Horizontal; Mouser PN 603-MFR-25FTF52-33K
R16, R19, R20, R25: 2k2; R_Axial_DIN0207_L6.3mm_D2.5mm_P7.62mm_Horizontal; Mouser PN 603-MF0207FTE52-2K2
R17: 100R; R_Axial_DIN0204_L3.6mm_D1.6mm_P5.08mm_Horizontal; Mouser PN 603-MFR-12FTF52-100R
R18: 1k; R_Axial_DIN0207_L6.3mm_D2.5mm_P7.62mm_Horizontal; Mouser PN 603-MFR-25FTF52-1K
R21: 560; R_Axial_DIN0309_L9.0mm_D3.2mm_P12.70mm_Horizontal; Mouser PN 603-FMP200JR-52-560R
R22, R23: 2R7; R_Axial_Power_L25.0mm_W9.0mm_P27.94mm; Mouser PN 603-SQP500JB-2R7
R24: 12k; R_Axial_DIN0207_L6.3mm_D2.5mm_P7.62mm_Horizontal; Mouser PN 603-MFR25SFTF26-12K
R26: 2R7; R_Axial_DIN0207_L6.3mm_D2.5mm_P7.62mm_Horizontal; Mouser PN 603-CFR-25JR-52-2R7

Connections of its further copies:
/amp-channel1/FB_DC: C12.2, C15.1, D13.1 (K), D14.2 (A), D15.1 (K), D16.2 (A), R16.2, R22.2, R23.1
/amp-channel1/VIN: C9.2; also elsewhere on the board
/amp-channel1/VOUT: C15.2, C16.1, R25.2; also elsewhere on the board
GND: C10.2, C14.2, Q8.1 (E), Q10.2 (C), Q12.2 (C), R15.2, R17.2, R18.2, R26.2; also elsewhere on the board
unnamed: C10.1, R14.1, R24.1
unnamed: C11.2, R17.1, R25.1
unnamed: C12.1, R19.2, R20.1
unnamed: C16.2, R26.1
unnamed: D9.2 (A), Q9.3 (B), R20.2
unnamed: D9.1 (K), D10.2 (A)
unnamed: D10.1 (K), D11.2 (A)
unnamed: D11.1 (K), D12.2 (A)
unnamed: C13.2, D12.1 (K), Q8.2 (C), Q10.3 (B)
unnamed: D13.2 (A), D15.2 (A), Q11.3 (E), R22.1
unnamed: D14.1 (K), D16.1 (K), Q12.3 (E), R23.2
unnamed: C9.1, Q7.2 (B), R14.2, R15.1
unnamed: C13.1, Q7.1 (C), Q8.3 (B), R18.1
unnamed: C11.1, Q7.3 (E), R16.1
unnamed: Q10.1 (E), Q12.1 (B), R21.2
unnamed: Q9.1 (E), Q11.1 (B), R21.1
VCC: C14.1, Q9.2 (C), Q11.2 (C), R19.1, R24.2; also elsewhere on the board

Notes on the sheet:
Zobel network
FB_AC

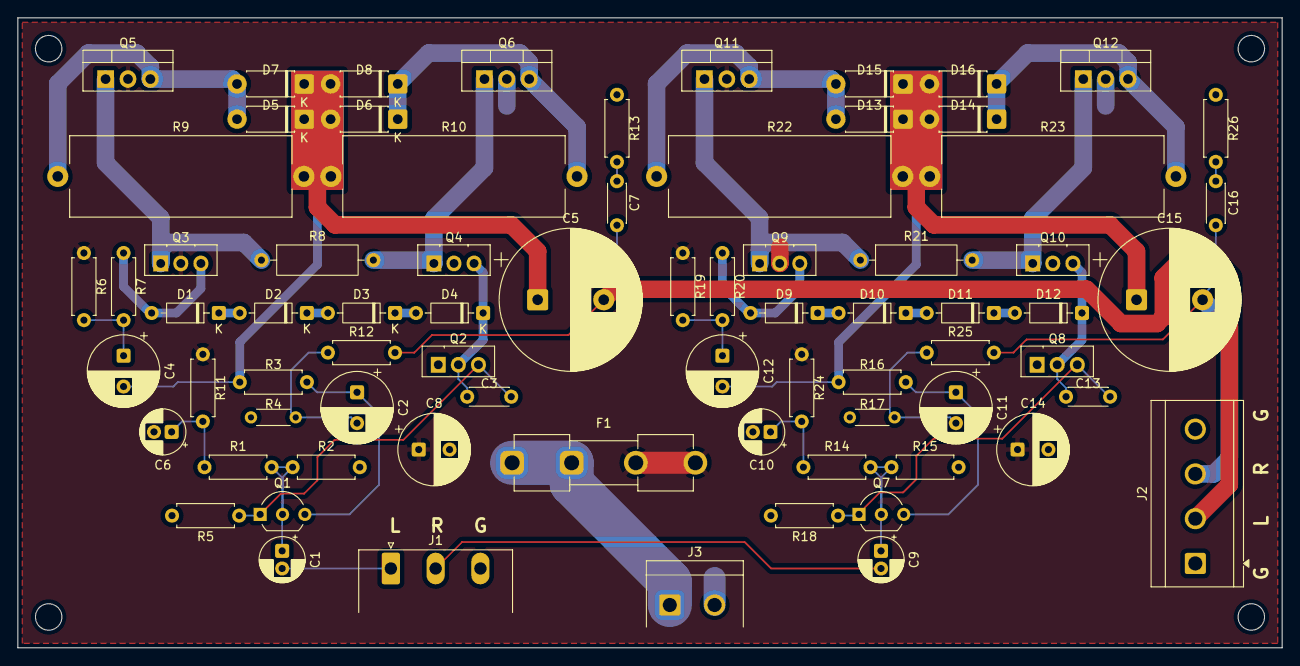
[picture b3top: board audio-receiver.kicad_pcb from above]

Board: 2 copper layers, 143.5 x 71.5 mm, 74 parts (0 on the bottom side), 41 nets.

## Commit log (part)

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2025-06-18 Initial project
2025-06-18 move PCB to dedicated directory
2025-06-18 fix project structure
2025-06-18 add simulation file
2025-06-19 create amplifier schematic
2025-06-20 edit amplifier schematic
2025-06-21 update schematic and start work on BOM
2025-06-23 add bom, edit symbols, assign some footprints
2025-06-24 update pcb/bom and add new schematic for input board
2025-06-24 improve current handling of pcb
2025-06-25 add schematic for input switcher
2025-06-25 input board schematic update
2025-06-25 remove unnecessary file
2025-06-25 lots of schematic + pcb updates
2025-06-25 fix submodule
2025-06-25 update control board schematic s
2025-06-26 bom, readme, cad, pcb
2025-06-26 update bom
2025-06-26 update CAD
2025-06-26 add bom to readme
2025-06-26 edit CAD
2025-06-26 update colors in cad
2025-06-29 bom edits
2025-07-03 fix power supply on pcb
